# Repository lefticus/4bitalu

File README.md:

# 4bitalu

[digikey BOM](https://www.digikey.com/en/mylists/list/D8YFZJU3KQ)

## Background

This project is derived from my ECPE 2504 class that I took at Virginia Tech. The project was submitted on March 18, 1998.

The goal of the class project was to create a "Nibble Slice ALU".

This was a project that had:

 * A 4 bit register (SR Latch Flip-Flop)
 * 4 bit opcode input
 * 4 bit operand input

We were allowed to use 7400 series TTL logic chips

 * 74153 4-bit multiplexers (x2)
 * 74175 Flip-Flop
 * 7483 4-bit adder
 * 7400 Quad NAND (x3)

The projects were built on breadboards with jumpers, switches, chips provided by the university (no pictures of the original were taken)

Requirements:

* 'A' input is the 4bit flip-flop
* 'B' input is a 4bit dip switch
* OpCode is a 4bit dip switch
* 8 instructions were required
  1. A <- A (Hold)
  2. A <- shr A (Shift-Right A)
  3. A <- A+B (Add B to A)
  4. A <- A+B+1 (Add B to A + 1)
  5. A <- A+1 (Increment A)
  6. A <- A' (Complement A)
  7. A <- 0 (Clear A)
  8. A <- A' OR B (Imply)

8 instructions were required - but we have 16 possible opcodes. That means we ended up with an additional 8 "unintended" or "undocumented" OpCodes!

The original product requirements doc follows:

## Original Design

## 2023 Build

I decided 25 years later to try my hand at PCB design and to actually build this old project. This took 2 revisions:

1. [Rev 1](df868067a174cf4c2a293e076a1fb69d7d88c638) had several issues
  * Power pins were not connected
  * Clock signal was not connected
  * All of the bits input to the adder were reversed because the new tool I was using (KiCad) had the pins in a different order compared to the schematics from 1998
  * The register LEDs were actually connected to the output of the adder, not to the output of the Flip-Flop (so I was reading what would be, not what currently was!)
2. [Rev 2](fc047236eafd9e9970c500b91abf409b33e64aa5) fixed those problems, and did not introduce any new ones, it does work!
  * Except that the pull-down resistors for the inputs are spec'd too high, so the carry-in bit to the adder was always around 1 volt.
  * This should not have been a problem, those adders should not register high unless the value is at least 2v, but it was always Carrying-In an extra bit (effectively every result was the expected result + 1)
  * Also many (optional) LEDs are added for observing the processes in play
3. Rev 3 is currently in process
  * Adds power filtering capacitors to the VCC of the 74's chips
  * Inverts the output of the clock switch (in rev2 down is high and up is low)
  * Adds an LED to show the current state of the clock input

These project files are all in KiCad format, if anyone wishes to fork / build their own / test this stuff out too

## Images

## Rev 1

Rev 1 Empty

Rev 1 Front

Rev 1 Back with bodge wires

## Rev 2

Rev 2 Empty

Rev 2 Running!

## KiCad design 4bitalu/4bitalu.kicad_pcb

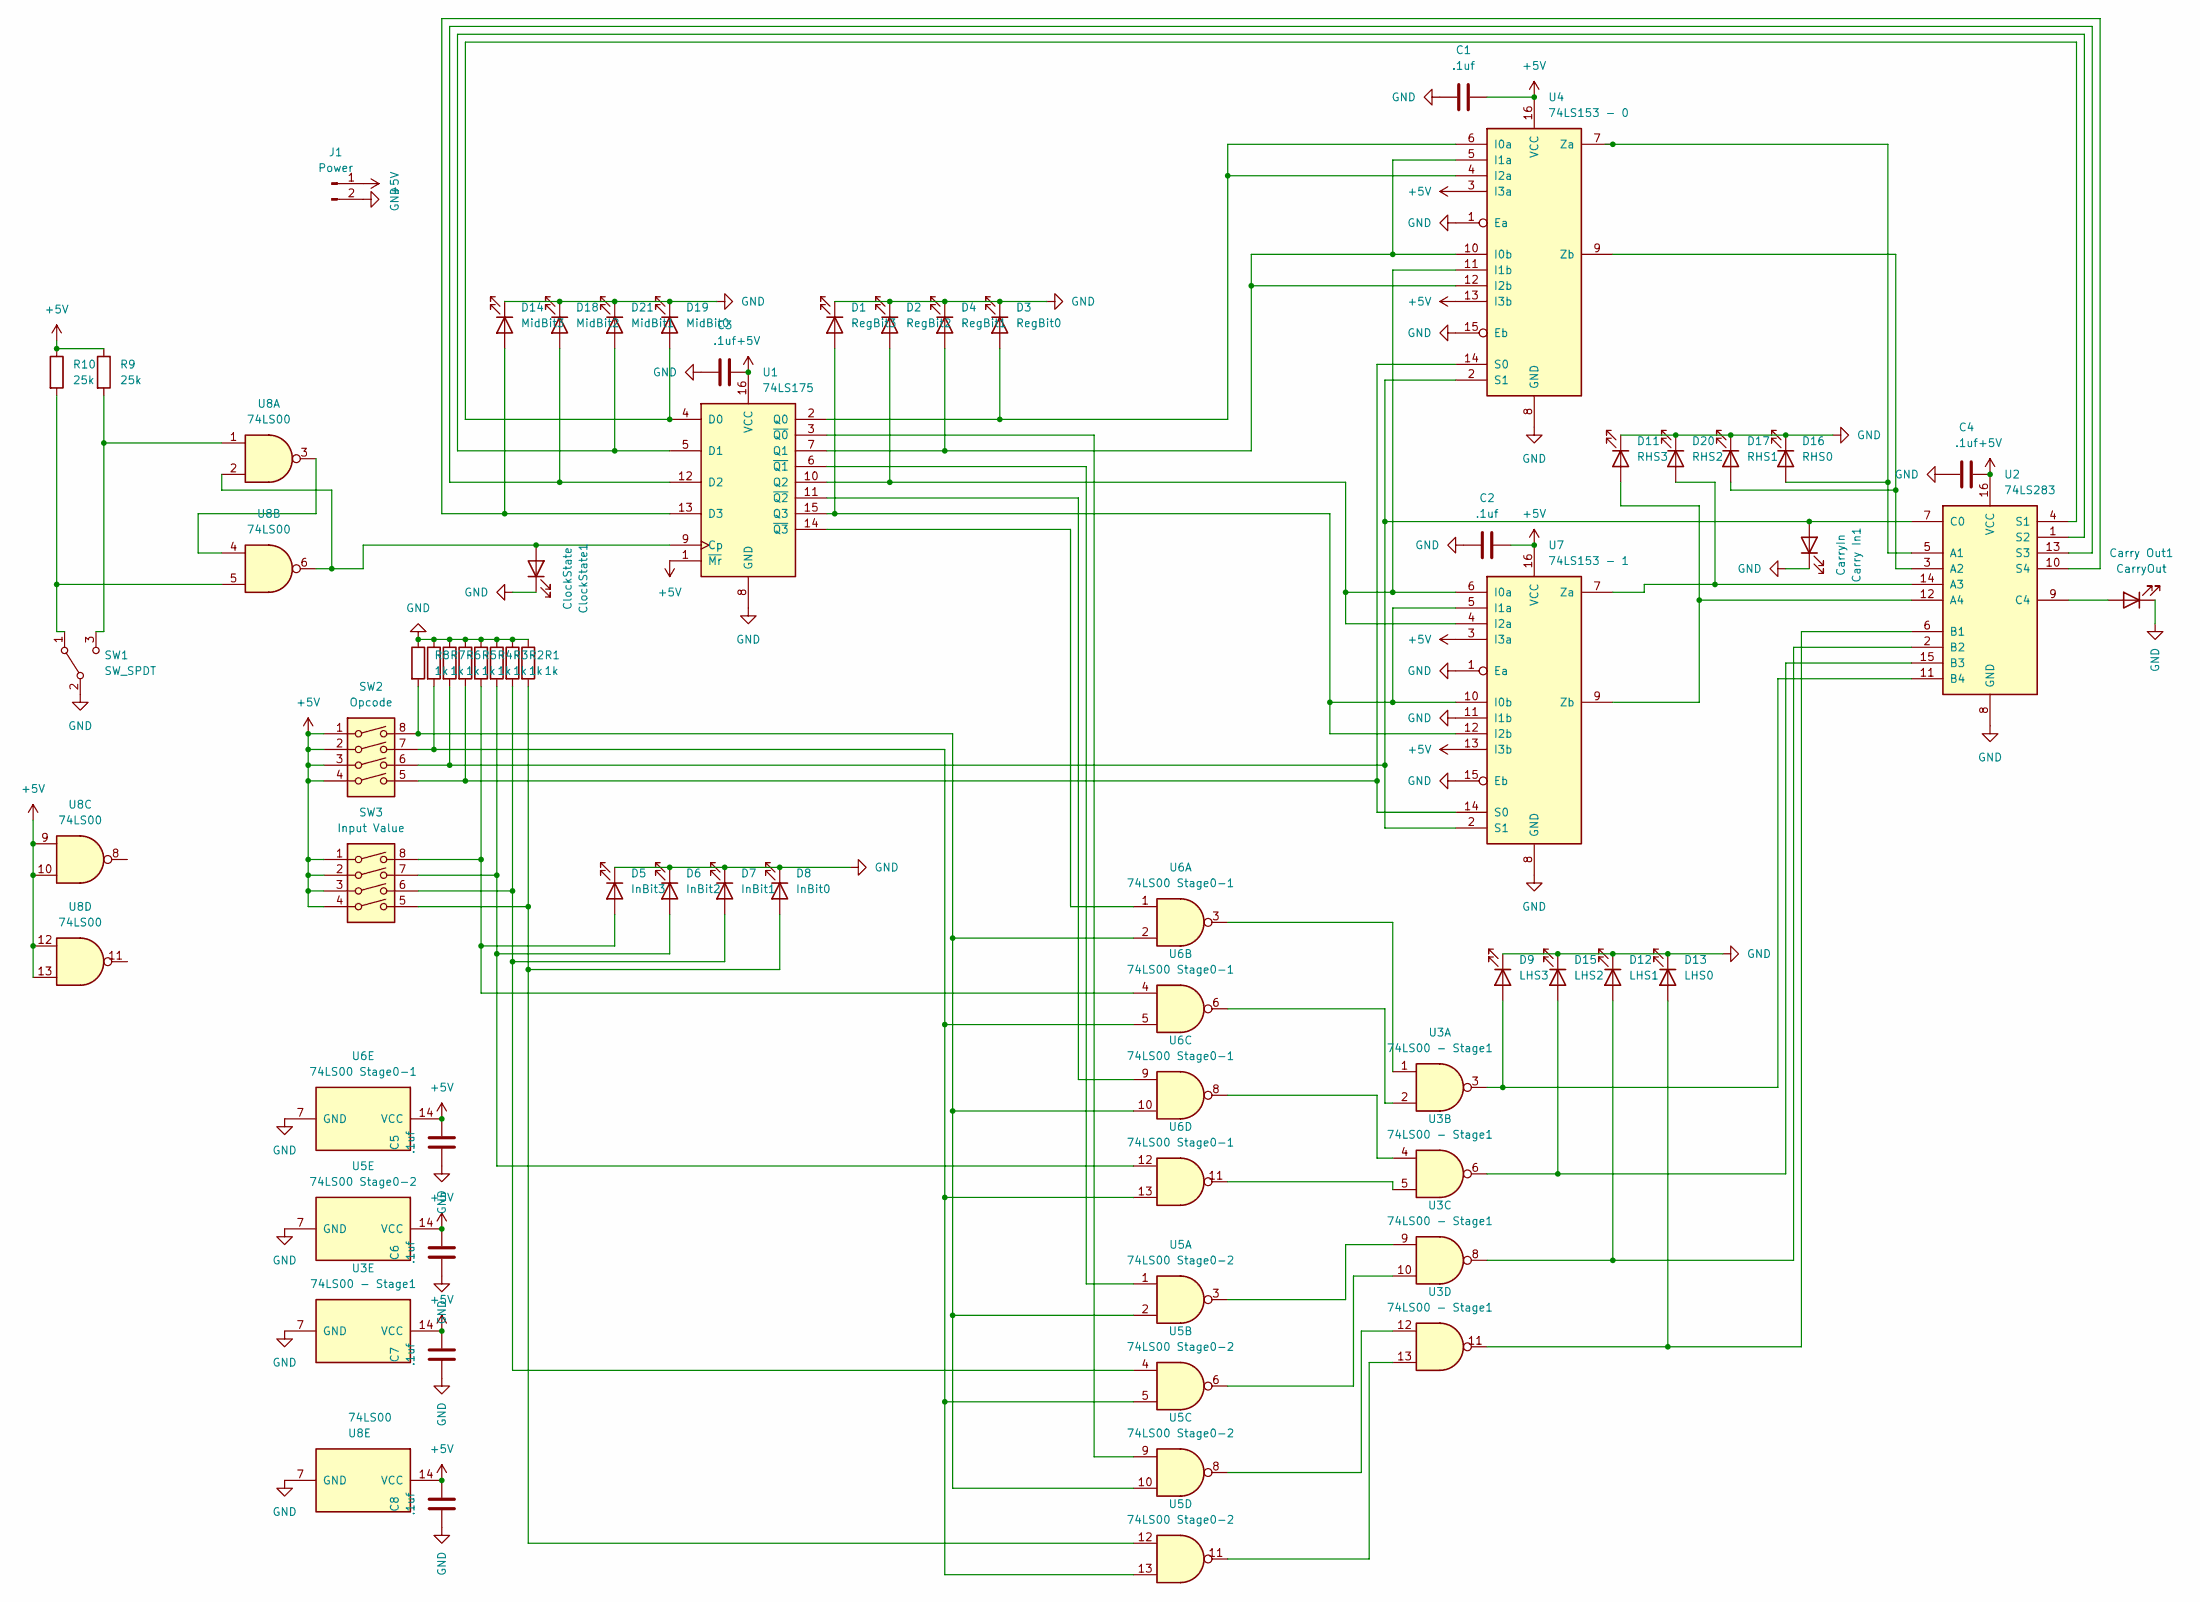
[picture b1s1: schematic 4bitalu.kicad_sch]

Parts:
C1, C2, C3, C4, C5, C6, C7, C8: .1uf; C_Disc_D3.0mm_W1.6mm_P2.50mm
Carry In1: CarryIn; LED_D3.0mm
Carry Out1: CarryOut; LED_D3.0mm
ClockState1: ClockState; LED_D3.0mm
D1: RegBit3; LED_D3.0mm
D2: RegBit2; LED_D3.0mm
D3: RegBit0; LED_D3.0mm
D4: RegBit1; LED_D3.0mm
D5: InBit3; LED_D3.0mm
D6: InBit2; LED_D3.0mm
D7: InBit1; LED_D3.0mm
D8: InBit0; LED_D3.0mm
D9: LHS3; LED_D3.0mm
D11: RHS3; LED_D3.0mm
D12: LHS1; LED_D3.0mm
D13: LHS0; LED_D3.0mm
D14: MidBit3; LED_D3.0mm
D15: LHS2; LED_D3.0mm
D16: RHS0; LED_D3.0mm
D17: RHS1; LED_D3.0mm
D18: MidBit2; LED_D3.0mm
D19: MidBit0; LED_D3.0mm
D20: RHS2; LED_D3.0mm
D21: MidBit1; LED_D3.0mm
J1: Power; PinHeader_1x02_P2.54mm_Vertical
R1, R2, R3, R4, R5, R6, R7, R8: 1k; R_Axial_DIN0207_L6.3mm_D2.5mm_P10.16mm_Horizontal
R9, R10: 25k; R_Axial_DIN0207_L6.3mm_D2.5mm_P10.16mm_Horizontal
SW1: SW_SPDT; SW_Slide_1P2T_CK_OS102011MS2Q
SW2: Opcode; DIP-8_W7.62mm
SW3: Input Value; DIP-8_W7.62mm
U1: 74LS175; DIP-16_W7.62mm
U2: 74LS283; DIP-16_W7.62mm
U3: 74LS00 - Stage1; DIP-14_W7.62mm
U4: 74LS153 - 0; DIP-16_W7.62mm
U5: 74LS00 Stage0-2; DIP-14_W7.62mm
U6: 74LS00 Stage0-1; DIP-14_W7.62mm
U7: 74LS153 - 1; DIP-16_W7.62mm
U8: 74LS00; DIP-14_W7.62mm

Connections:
+5V: C1.1, C2.1, C3.1, C4.1, C5.1, C6.1, C7.1, C8.1, J1.1, R9.1, R10.1, SW2.1, SW2.2, SW2.3, SW2.4, SW3.1, SW3.2, SW3.3, SW3.4, U1.1 (~Mr), U1.16 (VCC), U2.16 (VCC), U3.14 (VCC), U4.3 (I3a), U4.13 (I3b), U4.16 (VCC), U5.14 (VCC), U6.14 (VCC), U7.3 (I3a), U7.13 (I3b), U7.16 (VCC), U8.9, U8.10, U8.12, U8.13, U8.14 (VCC)
GND: C1.2, C2.2, C3.2, C4.2, C5.2, C6.2, C7.2, C8.2, Carry In1.1 (K), Carry Out1.1 (K), ClockState1.1 (K), D1.1 (K), D2.1 (K), D3.1 (K), D4.1 (K), D5.1 (K), D6.1 (K), D7.1 (K), D8.1 (K), D9.1 (K), D11.1 (K), D12.1 (K), D13.1 (K), D14.1 (K), D15.1 (K), D16.1 (K), D17.1 (K), D18.1 (K), D19.1 (K), D20.1 (K), D21.1 (K), J1.2, R1.1, R2.1, R3.1, R4.1, R5.1, R6.1, R7.1, R8.1, SW1.2 (B), U1.8 (GND), U2.8 (GND), U3.7 (GND), U4.1 (Ea), U4.8 (GND), U4.15 (Eb), U5.7 (GND), U6.7 (GND), U7.1 (Ea), U7.8 (GND), U7.11 (I1b), U7.15 (Eb), U8.7 (GND)
unnamed: Carry In1.2 (A), R6.2, SW2.6, U2.7 (C0), U4.2 (S1), U7.2 (S1)
unnamed: Carry Out1.2 (A), U2.9 (C4)
unnamed: ClockState1.2 (A), U1.9 (Cp), U8.2, U8.6
unnamed: D1.2 (A), U1.15 (Q3), U7.5 (I1a), U7.10 (I0b), U7.12 (I2b)
unnamed: D2.2 (A), U1.10 (Q2), U4.11 (I1b), U7.4 (I2a), U7.6 (I0a)
unnamed: D3.2 (A), U1.2 (Q0), U4.4 (I2a), U4.6 (I0a)
unnamed: D4.2 (A), U1.7 (Q1), U4.5 (I1a), U4.10 (I0b), U4.12 (I2b)
unnamed: D5.2 (A), R4.2, SW3.8, U6.4
unnamed: D6.2 (A), R3.2, SW3.7, U6.12
unnamed: D7.2 (A), R2.2, SW3.6, U5.4
unnamed: D8.2 (A), R1.2, SW3.5, U5.12
unnamed: D9.2 (A), U2.11 (B4), U3.3
unnamed: D11.2 (A), U2.12 (A4), U7.9 (Zb)
unnamed: D12.2 (A), U2.2 (B2), U3.8
unnamed: D13.2 (A), U2.6 (B1), U3.11
unnamed: D14.2 (A), U1.13 (D3), U2.10 (S4)
unnamed: D15.2 (A), U2.15 (B3), U3.6
unnamed: D16.2 (A), U2.5 (A1), U4.7 (Za)
unnamed: D17.2 (A), U2.3 (A2), U4.9 (Zb)
unnamed: D18.2 (A), U1.12 (D2), U2.13 (S3)
unnamed: D19.2 (A), U1.4 (D0), U2.4 (S1)
unnamed: D20.2 (A), U2.14 (A3), U7.7 (Za)
unnamed: D21.2 (A), U1.5 (D1), U2.1 (S2)
unnamed: R7.2, SW2.7, U5.5, U5.13, U6.5, U6.13
unnamed: R8.2, SW2.8, U5.2, U5.10, U6.2, U6.10
unnamed: R10.2, SW1.1 (A), U8.5
unnamed: R9.2, SW1.3 (C), U8.1
unnamed: U1.3 (~Q0), U5.9
unnamed: U1.6 (~Q1), U5.1
unnamed: U1.11 (~Q2), U6.9
unnamed: U1.14 (~Q3), U6.1
unnamed: U3.1, U6.3
unnamed: U3.2, U6.6
unnamed: U3.4, U6.8
unnamed: U3.5, U6.11
unnamed: U3.9, U5.3
unnamed: U3.10, U5.6
unnamed: U3.12, U5.8
unnamed: U3.13, U5.11
unnamed: R5.2, SW2.5, U4.14 (S0), U7.14 (S0)
unnamed: U8.3, U8.4

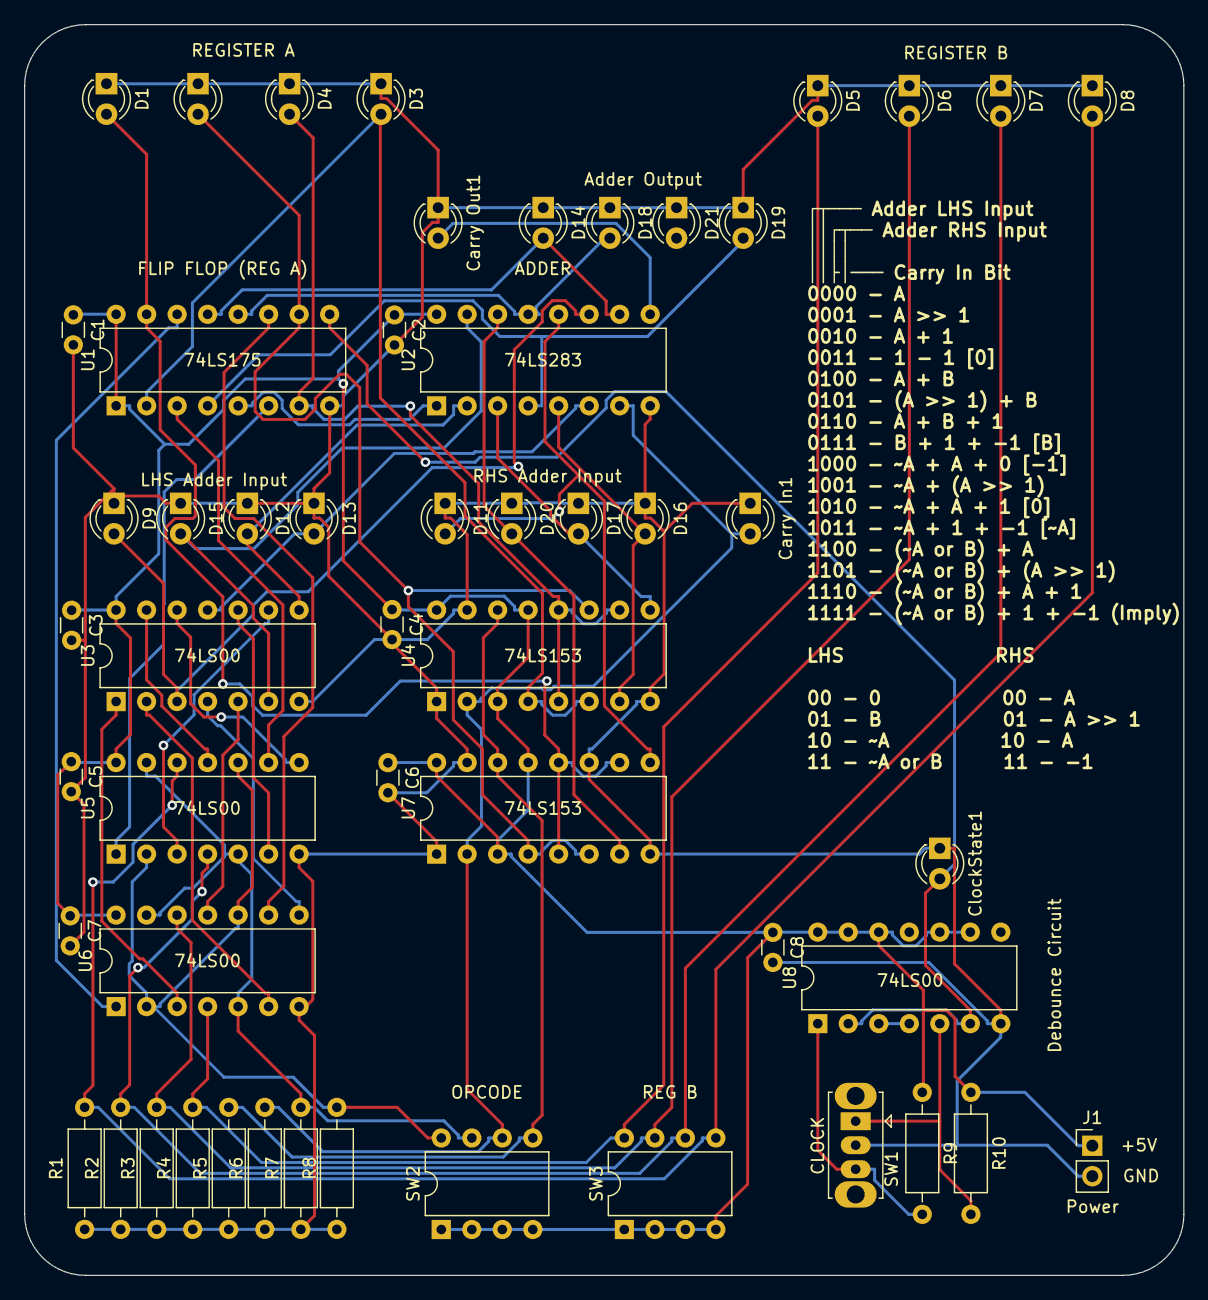
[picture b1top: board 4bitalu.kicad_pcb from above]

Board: 2 copper layers, 96.5 x 104.1 mm, 53 parts (0 on the bottom side), 43 nets.

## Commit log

2023-11-30 Initial PCB generated
2023-11-30 Rev 2 of PCB design
    Known issues:
    * Pulldown resistors are too high (should be 1k)
    * Missing capacitors for power inputs on chips
    * Inputs on unused NAND gates are not tied high
    * Clock switch is in unexepected orientation
2023-11-30 Revision 3 mostly ready
    * Adds caps on power
    * Inverts logic for clock switch
    * Adds optional clock LED
    * Changes pulldown resistors to 1k
    Note: this design should also work with 3.3v logic and LEDs
2023-11-30 Add original documentation
2023-11-30 Rename 4 Stages Combined.png to 4StagesCombined.png
2023-11-30 Add board images
2023-11-30 Finish documenting process / status
2023-11-30 Add link to BOM for digikey
2023-12-09 Initial take on a 3d printable design for the case
